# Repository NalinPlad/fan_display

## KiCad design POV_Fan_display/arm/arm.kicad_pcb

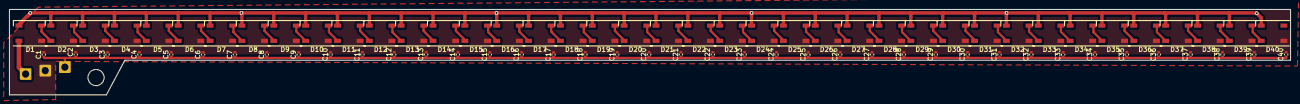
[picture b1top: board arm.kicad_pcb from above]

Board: 2 copper layers, 277.5 x 18.5 mm, 83 parts (0 on the bottom side), 42 nets.

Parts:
C1, C2, C3, C4, C5, C6, C7, C8, C9, C10, C11, C12, C13, C14, C15, C16, C17, C18, C19, C20, C21, C22, C23, C24, C25, C26, C27, C28, C29, C30, C31, C32, C33, C34, C35, C36, C37, C38, C39, C40: 0.1uF; C_0402_1005Metric
D1, D2, D3, D4, D5, D6, D7, D8, D9, D10, D11, D12, D13, D14, D15, D16, D17, D18, D19, D20, D21, D22, D23, D24, D25, D26, D27, D28, D29, D30, D31, D32, D33, D34, D35, D36, D37, D38, D39, D40: WS2812B; LED_WS2812B_PLCC4_5.0x5.0mm_P3.2mm
J1: Ring_1; SolderWire-0.75sqmm_1x01_D1.25mm_OD2.3mm
J2: Ring_2; SolderWire-0.75sqmm_1x01_D1.25mm_OD2.3mm
J3: Ring_3; SolderWire-0.75sqmm_1x01_D1.25mm_OD2.3mm

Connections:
+5V: C1.2, C2.2, C3.2, C4.2, C5.2, C6.2, C7.2, C8.2, C9.2, C10.2, C11.2, C12.2, C13.2, C14.2, C15.2, C16.2, C17.2, C18.2, C19.2, C20.2, C21.2, C22.2, C23.2, C24.2, C25.2, C26.2, C27.2, C28.2, C29.2, C30.2, C31.2, C32.2, C33.2, C34.2, C35.2, C36.2, C37.2, C38.2, C39.2, C40.2, D1.1 (VDD), D2.1 (VDD), D3.1 (VDD), D4.1 (VDD), D5.1 (VDD), D6.1 (VDD), D7.1 (VDD), D8.1 (VDD), D9.1 (VDD), D10.1 (VDD), D11.1 (VDD), D12.1 (VDD), D13.1 (VDD), D14.1 (VDD), D15.1 (VDD), D16.1 (VDD), D17.1 (VDD), D18.1 (VDD), D19.1 (VDD), D20.1 (VDD), D21.1 (VDD), D22.1 (VDD), D23.1 (VDD), D24.1 (VDD), D25.1 (VDD), D26.1 (VDD), D27.1 (VDD), D28.1 (VDD), D29.1 (VDD), D30.1 (VDD), D31.1 (VDD), D32.1 (VDD), D33.1 (VDD), D34.1 (VDD), D35.1 (VDD), D36.1 (VDD), D37.1 (VDD), D38.1 (VDD), D39.1 (VDD), D40.1 (VDD), J1.1
/DIN: D1.4 (DIN), J3.1
/LEDs_with_caps_1/DOUT: D8.2 (DOUT), D9.4 (DIN)
/LEDs_with_caps_2/DOUT: D16.2 (DOUT), D17.4 (DIN)
/LEDs_with_caps_3/DOUT: D24.2 (DOUT), D25.4 (DIN)
/LEDs_with_caps_4/DOUT: D32.2 (DOUT), D33.4 (DIN)
GND: C1.1, C2.1, C3.1, C4.1, C5.1, C6.1, C7.1, C8.1, C9.1, C10.1, C11.1, C12.1, C13.1, C14.1, C15.1, C16.1, C17.1, C18.1, C19.1, C20.1, C21.1, C22.1, C23.1, C24.1, C25.1, C26.1, C27.1, C28.1, C29.1, C30.1, C31.1, C32.1, C33.1, C34.1, C35.1, C36.1, C37.1, C38.1, C39.1, C40.1, D1.3 (VSS), D2.3 (VSS), D3.3 (VSS), D4.3 (VSS), D5.3 (VSS), D6.3 (VSS), D7.3 (VSS), D8.3 (VSS), D9.3 (VSS), D10.3 (VSS), D11.3 (VSS), D12.3 (VSS), D13.3 (VSS), D14.3 (VSS), D15.3 (VSS), D16.3 (VSS), D17.3 (VSS), D18.3 (VSS), D19.3 (VSS), D20.3 (VSS), D21.3 (VSS), D22.3 (VSS), D23.3 (VSS), D24.3 (VSS), D25.3 (VSS), D26.3 (VSS), D27.3 (VSS), D28.3 (VSS), D29.3 (VSS), D30.3 (VSS), D31.3 (VSS), D32.3 (VSS), D33.3 (VSS), D34.3 (VSS), D35.3 (VSS), D36.3 (VSS), D37.3 (VSS), D38.3 (VSS), D39.3 (VSS), D40.3 (VSS), J2.1
unnamed: D1.2 (DOUT), D2.4 (DIN)
unnamed: D2.2 (DOUT), D3.4 (DIN)
unnamed: D3.2 (DOUT), D4.4 (DIN)
unnamed: D4.2 (DOUT), D5.4 (DIN)
unnamed: D5.2 (DOUT), D6.4 (DIN)
unnamed: D6.2 (DOUT), D7.4 (DIN)
unnamed: D7.2 (DOUT), D8.4 (DIN)
unnamed: D9.2 (DOUT), D10.4 (DIN)
unnamed: D10.2 (DOUT), D11.4 (DIN)
unnamed: D11.2 (DOUT), D12.4 (DIN)
unnamed: D12.2 (DOUT), D13.4 (DIN)
unnamed: D13.2 (DOUT), D14.4 (DIN)
unnamed: D14.2 (DOUT), D15.4 (DIN)
unnamed: D15.2 (DOUT), D16.4 (DIN)
unnamed: D17.2 (DOUT), D18.4 (DIN)
unnamed: D18.2 (DOUT), D19.4 (DIN)
unnamed: D19.2 (DOUT), D20.4 (DIN)
unnamed: D20.2 (DOUT), D21.4 (DIN)
unnamed: D21.2 (DOUT), D22.4 (DIN)
unnamed: D22.2 (DOUT), D23.4 (DIN)
unnamed: D23.2 (DOUT), D24.4 (DIN)
unnamed: D25.2 (DOUT), D26.4 (DIN)
unnamed: D26.2 (DOUT), D27.4 (DIN)
unnamed: D27.2 (DOUT), D28.4 (DIN)
unnamed: D28.2 (DOUT), D29.4 (DIN)
unnamed: D29.2 (DOUT), D30.4 (DIN)
unnamed: D30.2 (DOUT), D31.4 (DIN)
unnamed: D31.2 (DOUT), D32.4 (DIN)
unnamed: D33.2 (DOUT), D34.4 (DIN)
unnamed: D34.2 (DOUT), D35.4 (DIN)
unnamed: D35.2 (DOUT), D36.4 (DIN)
unnamed: D36.2 (DOUT), D37.4 (DIN)
unnamed: D37.2 (DOUT), D38.4 (DIN)
unnamed: D38.2 (DOUT), D39.4 (DIN)
unnamed: D39.2 (DOUT), D40.4 (DIN)

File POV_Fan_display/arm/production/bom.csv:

Designator,Footprint,Quantity,Value,LCSC Part #
"C1, C10, C11, C12, C13, C14, C15, C16, C17, C18, C19, C2, C20, C21, C22, C23, C24, C25, C26, C27, C28, C29, C3, C30, C31, C32, C33, C34, C35, C36, C37, C38, C39, C4, C40, C5, C6, C7, C8, C9",0402,40,0.1uF,
"D1, D10, D11, D12, D13, D14, D15, D16, D17, D18, D19, D2, D20, D21, D22, D23, D24, D25, D26, D27, D28, D29, D3, D30, D31, D32, D33, D34, D35, D36, D37, D38, D39, D4, D40, D5, D6, D7, D8, D9",LED_WS2812B_PLCC4_5.0x5.0mm_P3.2mm,40,WS2812B,
J1,SolderWire-0.75sqmm_1x01_D1.25mm_OD2.3mm,1,Ring_1,
J2,SolderWire-0.75sqmm_1x01_D1.25mm_OD2.3mm,1,Ring_2,
J3,SolderWire-0.75sqmm_1x01_D1.25mm_OD2.3mm,1,Ring_3,

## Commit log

2024-09-30 init
2024-09-30 two blades
2024-09-30 add rp2040
2024-10-01 add power supply to rp2040
2024-10-01 seperate fans
2024-10-04 kicad backup
2024-10-05 add flash storage
2024-10-09 make 8 led groups for easier PCB duplication
2024-10-09 make smaller design for prototyping
2024-10-09 get rid of second arm, just ordering two now
2024-10-11 route alot
2024-10-11 ready to print
2024-10-13 route plane a little different
2024-10-26 starting 3D printing
2024-10-28 starting 3d fixing
2024-11-04 bump version
2024-12-06 final rev, working on spinn disp now
